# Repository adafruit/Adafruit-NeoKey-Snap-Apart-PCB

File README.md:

## Adafruit NeoKey Snap-Apart 5x6 Ortho Mechanical Key Switches with NeoPixel PCB

<a href="http://www.adafruit.com/products/5157"><br/>
Click here to purchase one from the Adafruit shop</a>

PCB files for the Adafruit NeoKey Snap-Apart 5x6 Ortho Mechanical Key Switches with NeoPixel. 

Format is EagleCAD schematic and board layout
* https://www.adafruit.com/product/5157

### Description

For folks who want ready-to-go keeb action, we've got the lovely Adafruit Macropad with a 3x4 grid of MX+NeoPixel key switches - but for those who like to forge their own path, we now present the easiest way of creating custom ortholinear (that's a fancy word for gridded) key matrices. Instead of hand soldering together a custom matrix of NeoKey socket breakouts, the Adafruit NeoKey 5x6 Ortho Snap-Apart Mechanical Key Switches with NeoPixel has 30 key switches that can be snapped apart to make any size grid.

That's right! Even though it comes as 5x6, you can turn it into 2x3, 1x6, 4x3...whatever you wish, and it will work just the way you expect. The little break-apart tabs have traces running through them that pass the power, NeoPixel, and keymatrix lines up and down.

Each 'sub-key' is the same - with a column and row line that is diode protected. For whatever grid size you eventually choose, connect a digital IO pin from your microcontroller to each of the outer rows and columns. With the diode, you don't have to worry about key ghosting.

If you want to add glowy goodness, that's even easier. Each key also has a single reverse-mount NeoPixel pointing up through the spot where many switches would have an LED to shine through. Connect 3 to 5V power to any of the + and - pins on the grid, and connect a single digital IO line to the beginning of the 'NeoPixel snake' that winds its way through the matrix. A weak 2.2K pass-through resistor will shunt data through at the end of each row, so you don't have to do any jumpering unless the matrix is not-rectangular.

Every breakout has a Kailh socket, which means you can plug in any MX-compatible switch instead of soldering it in. You may need a little glue to keep the switch in place: hot glue or a dot of epoxy worked fine for us. The sub-keys are spaced 0.75" apart for compact keebing. There's large 0.125" mounting holes at the corners of each key for easy mounting to a backplane.

Please note, each order comes with one sheet of assembled PCBs that can be broken apart - we include top and bottom railing bits to help keep it nice and flat during shipment. Once the grid is broken, you could jumper the breakout pads together to re-connect but it won't be very fun. Mechanical switches and keycaps are not included! Use any MX-compatible switch: Kailh, Gateron, etc all work!

### License

Adafruit invests time and resources providing this open source design, please support Adafruit and open-source hardware by purchasing products from [Adafruit](https://www.adafruit.com)!

Designed by Limor Fried/Ladyada for Adafruit Industries.

Creative Commons Attribution/Share-Alike, all text above must be included in any redistribution. 
See license.txt for additional details.

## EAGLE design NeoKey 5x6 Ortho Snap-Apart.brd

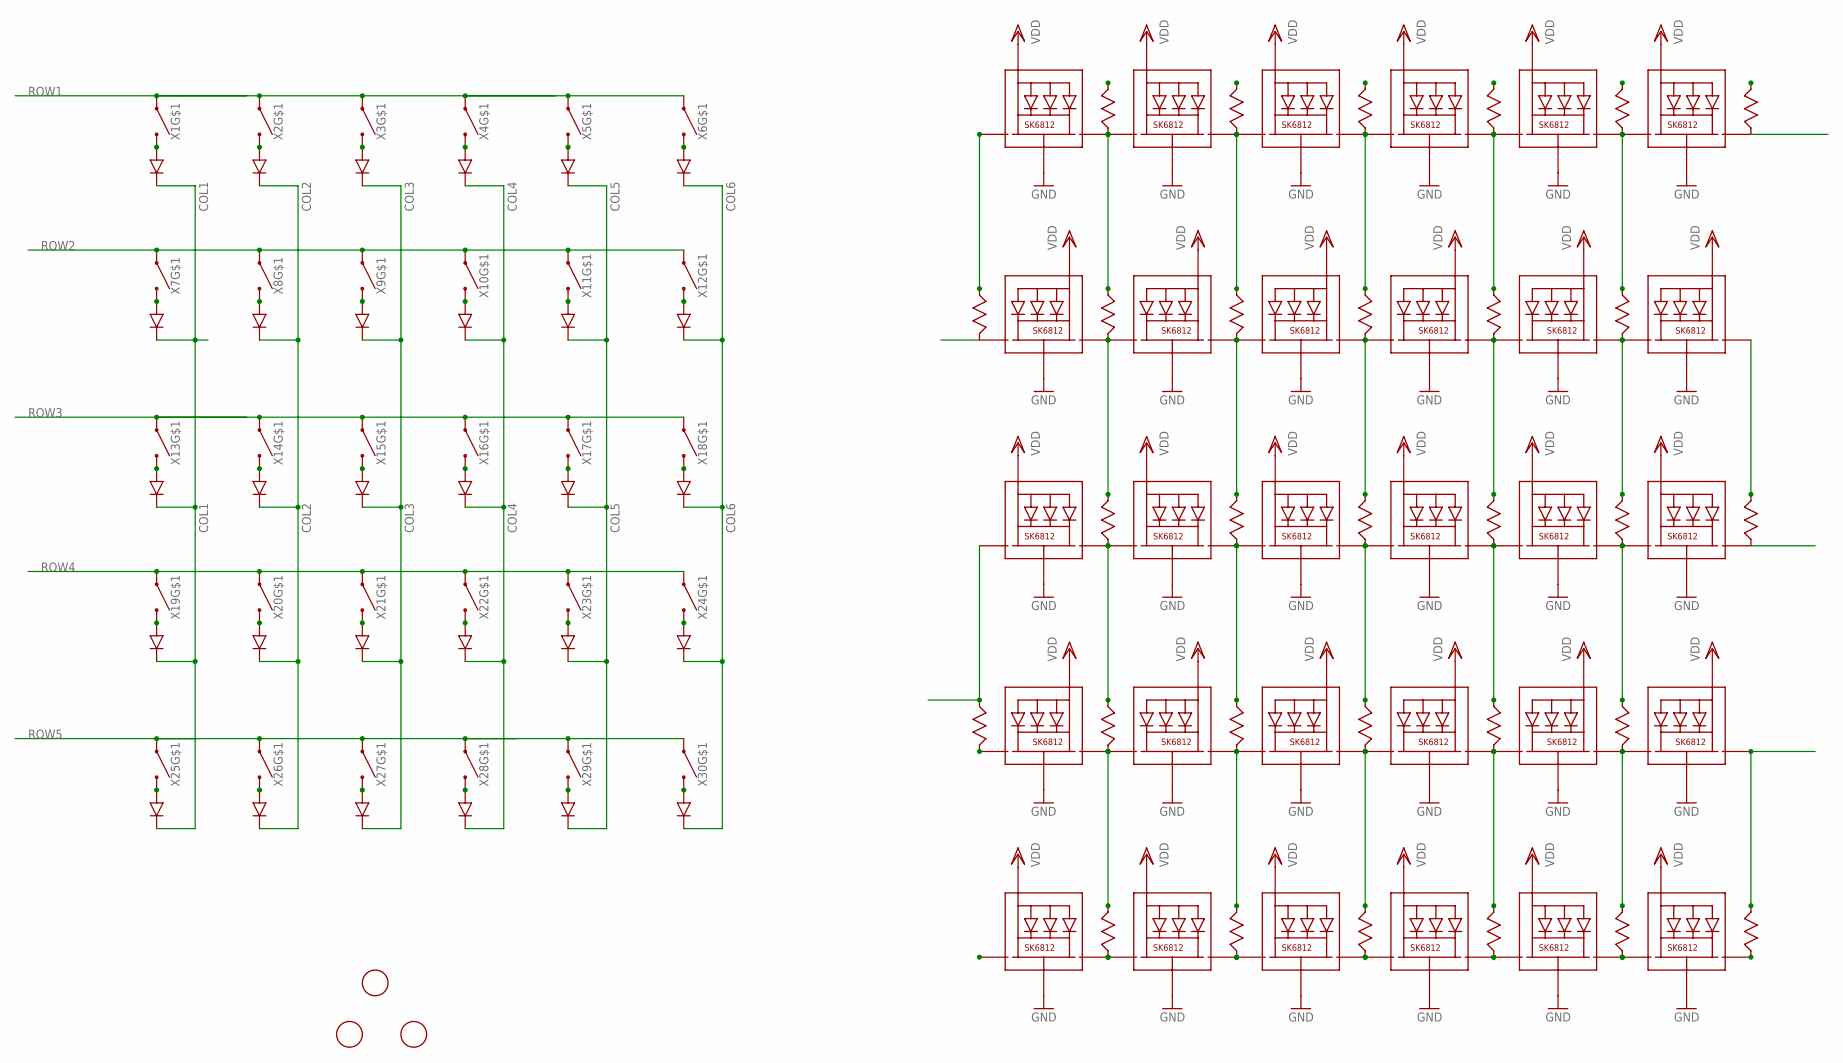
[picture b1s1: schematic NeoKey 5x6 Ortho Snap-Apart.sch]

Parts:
U$1, U$2, U$3: FIDUCIAL; FIDUCIAL_1MM
X1, X2, X3, X4, X5, X6, X13, X14, X15, X16, X17, X18, X25, X26, X27, X28, X29, X30: KAILH_SOCKET_TILE
X7, X8, X9, X10, X11, X12, X19, X20, X21, X22, X23, X24: KAILH_SOCKET_TILE_REVERSE; KAILH_SOCKET_TILE_REV

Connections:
COL1: X1.C (SW_C), X1.C1 (SW_C), X1.C2 (SW_C), X7.C (SW_C), X7.C1 (SW_C), X7.C2 (SW_C), X13.C (SW_C), X13.C1 (SW_C), X13.C2 (SW_C), X19.C (SW_C), X19.C1 (SW_C), X19.C2 (SW_C), X25.C (SW_C), X25.C1 (SW_C), X25.C2 (SW_C)
COL2: X2.C (SW_C), X2.C1 (SW_C), X2.C2 (SW_C), X8.C (SW_C), X8.C1 (SW_C), X8.C2 (SW_C), X14.C (SW_C), X14.C1 (SW_C), X14.C2 (SW_C), X20.C (SW_C), X20.C1 (SW_C), X20.C2 (SW_C), X26.C (SW_C), X26.C1 (SW_C), X26.C2 (SW_C)
COL3: X3.C (SW_C), X3.C1 (SW_C), X3.C2 (SW_C), X9.C (SW_C), X9.C1 (SW_C), X9.C2 (SW_C), X15.C (SW_C), X15.C1 (SW_C), X15.C2 (SW_C), X21.C (SW_C), X21.C1 (SW_C), X21.C2 (SW_C), X27.C (SW_C), X27.C1 (SW_C), X27.C2 (SW_C)
COL4: X4.C (SW_C), X4.C1 (SW_C), X4.C2 (SW_C), X10.C (SW_C), X10.C1 (SW_C), X10.C2 (SW_C), X16.C (SW_C), X16.C1 (SW_C), X16.C2 (SW_C), X22.C (SW_C), X22.C1 (SW_C), X22.C2 (SW_C), X28.C (SW_C), X28.C1 (SW_C), X28.C2 (SW_C)
COL5: X5.C (SW_C), X5.C1 (SW_C), X5.C2 (SW_C), X11.C (SW_C), X11.C1 (SW_C), X11.C2 (SW_C), X17.C (SW_C), X17.C1 (SW_C), X17.C2 (SW_C), X23.C (SW_C), X23.C1 (SW_C), X23.C2 (SW_C), X29.C (SW_C), X29.C1 (SW_C), X29.C2 (SW_C)
COL6: X6.C (SW_C), X6.C1 (SW_C), X6.C2 (SW_C), X12.C (SW_C), X12.C1 (SW_C), X12.C2 (SW_C), X18.C (SW_C), X18.C1 (SW_C), X18.C2 (SW_C), X24.C (SW_C), X24.C1 (SW_C), X24.C2 (SW_C), X30.C (SW_C), X30.C1 (SW_C), X30.C2 (SW_C)
GND: X1.3-GND (GND), X1.C- (GND), X1.GND1 (GND), X1.GND2 (GND), X2.3-GND (GND), X2.C- (GND), X2.GND1 (GND), X2.GND2 (GND), X3.3-GND (GND), X3.C- (GND), X3.GND1 (GND), X3.GND2 (GND), X4.3-GND (GND), X4.C- (GND), X4.GND1 (GND), X4.GND2 (GND), X5.3-GND (GND), X5.C- (GND), X5.GND1 (GND), X5.GND2 (GND), X6.3-GND (GND), X6.C- (GND), X6.GND1 (GND), X6.GND2 (GND), X7.3-GND (GND), X7.C- (GND), X7.GND1 (GND), X7.GND2 (GND), X8.3-GND (GND), X8.C- (GND), X8.GND1 (GND), X8.GND2 (GND), X9.3-GND (GND), X9.C- (GND), X9.GND1 (GND), X9.GND2 (GND), X10.3-GND (GND), X10.C- (GND), X10.GND1 (GND), X10.GND2 (GND), X11.3-GND (GND), X11.C- (GND), X11.GND1 (GND), X11.GND2 (GND), X12.3-GND (GND), X12.C- (GND), X12.GND1 (GND), X12.GND2 (GND), X13.3-GND (GND), X13.C- (GND), X13.GND1 (GND), X13.GND2 (GND), X14.3-GND (GND), X14.C- (GND), X14.GND1 (GND), X14.GND2 (GND), X15.3-GND (GND), X15.C- (GND), X15.GND1 (GND), X15.GND2 (GND), X16.3-GND (GND), X16.C- (GND), X16.GND1 (GND), X16.GND2 (GND), X17.3-GND (GND), X17.C- (GND), X17.GND1 (GND), X17.GND2 (GND), X18.3-GND (GND), X18.C- (GND), X18.GND1 (GND), X18.GND2 (GND), X19.3-GND (GND), X19.C- (GND), X19.GND1 (GND), X19.GND2 (GND), X20.3-GND (GND), X20.C- (GND), X20.GND1 (GND), X20.GND2 (GND), X21.3-GND (GND), X21.C- (GND), X21.GND1 (GND), X21.GND2 (GND), X22.3-GND (GND), X22.C- (GND), X22.GND1 (GND), X22.GND2 (GND), X23.3-GND (GND), X23.C- (GND), X23.GND1 (GND), X23.GND2 (GND), X24.3-GND (GND), X24.C- (GND), X24.GND1 (GND), X24.GND2 (GND), X25.3-GND (GND), X25.C- (GND), X25.GND1 (GND), X25.GND2 (GND), X26.3-GND (GND), X26.C- (GND), X26.GND1 (GND), X26.GND2 (GND), X27.3-GND (GND), X27.C- (GND), X27.GND1 (GND), X27.GND2 (GND), X28.3-GND (GND), X28.C- (GND), X28.GND1 (GND), X28.GND2 (GND), X29.3-GND (GND), X29.C- (GND), X29.GND1 (GND), X29.GND2 (GND), X30.3-GND (GND), X30.C- (GND), X30.GND1 (GND), X30.GND2 (GND)
unnamed: X1.4-DIN (DI), X1.DIN (DI), X1.DIN1 (DI), X2.2-DOUT (DO), X2.DOUT (DO), X2.DOUT1 (DO), X8.DIN_C (DI1), X8.DIN_C1 (DI1)
unnamed: X1.D+ (DA), X1.DA
unnamed: X1.DIN_C (DI1), X1.DIN_C1 (DI1)
unnamed: X2.D+ (DA), X2.DA
unnamed: X4.D+ (DA), X4.DA
unnamed: X1.2-DOUT (DO), X1.DOUT (DO), X1.DOUT1 (DO), X7.DIN_C (DI1), X7.DIN_C1 (DI1)
unnamed: X7.D+ (DA), X7.DA
unnamed: X2.DIN_C (DI1), X2.DIN_C1 (DI1)
unnamed: X3.D+ (DA), X3.DA
unnamed: X2.4-DIN (DI), X2.DIN (DI), X2.DIN1 (DI), X3.2-DOUT (DO), X3.DOUT (DO), X3.DOUT1 (DO), X9.DIN_C (DI1), X9.DIN_C1 (DI1)
unnamed: X3.4-DIN (DI), X3.DIN (DI), X3.DIN1 (DI), X4.2-DOUT (DO), X4.DOUT (DO), X4.DOUT1 (DO), X10.DIN_C (DI1), X10.DIN_C1 (DI1)
unnamed: X3.DIN_C (DI1), X3.DIN_C1 (DI1)
unnamed: X4.4-DIN (DI), X4.DIN (DI), X4.DIN1 (DI), X5.2-DOUT (DO), X5.DOUT (DO), X5.DOUT1 (DO), X11.DIN_C (DI1), X11.DIN_C1 (DI1)
unnamed: X4.DIN_C (DI1), X4.DIN_C1 (DI1)
unnamed: X6.D+ (DA), X6.DA
unnamed: X5.4-DIN (DI), X5.DIN (DI), X5.DIN1 (DI), X6.2-DOUT (DO), X6.DOUT (DO), X6.DOUT1 (DO), X12.DIN_C (DI1), X12.DIN_C1 (DI1)
unnamed: X12.2-DOUT (DO), X12.DOUT (DO), X12.DOUT1 (DO), X18.DIN_C (DI1), X18.DIN_C1 (DI1)
unnamed: X6.DIN_C (DI1), X6.DIN_C1 (DI1)
unnamed: X5.D+ (DA), X5.DA
unnamed: X5.DIN_C (DI1), X5.DIN_C1 (DI1)
unnamed: X6.4-DIN (DI), X6.DIN (DI), X6.DIN1 (DI)
unnamed: X13.D+ (DA), X13.DA
unnamed: X8.D+ (DA), X8.DA
unnamed: X8.2-DOUT (DO), X8.DOUT (DO), X8.DOUT1 (DO), X9.4-DIN (DI), X9.DIN (DI), X9.DIN1 (DI), X14.DIN_C (DI1), X14.DIN_C1 (DI1)
unnamed: X13.2-DOUT (DO), X13.DOUT (DO), X13.DOUT1 (DO), X19.DIN_C (DI1), X19.DIN_C1 (DI1)
unnamed: X9.D+ (DA), X9.DA
unnamed: X9.2-DOUT (DO), X9.DOUT (DO), X9.DOUT1 (DO), X10.4-DIN (DI), X10.DIN (DI), X10.DIN1 (DI), X15.DIN_C (DI1), X15.DIN_C1 (DI1)
unnamed: X13.4-DIN (DI), X13.DIN (DI), X13.DIN1 (DI), X14.2-DOUT (DO), X14.DOUT (DO), X14.DOUT1 (DO), X20.DIN_C (DI1), X20.DIN_C1 (DI1)
unnamed: X10.D+ (DA), X10.DA
unnamed: X10.2-DOUT (DO), X10.DOUT (DO), X10.DOUT1 (DO), X11.4-DIN (DI), X11.DIN (DI), X11.DIN1 (DI), X16.DIN_C (DI1), X16.DIN_C1 (DI1)
unnamed: X7.2-DOUT (DO), X7.DOUT (DO), X7.DOUT1 (DO), X8.4-DIN (DI), X8.DIN (DI), X8.DIN1 (DI), X13.DIN_C (DI1), X13.DIN_C1 (DI1)
unnamed: X11.D+ (DA), X11.DA
unnamed: X11.2-DOUT (DO), X11.DOUT (DO), X11.DOUT1 (DO), X12.4-DIN (DI), X12.DIN (DI), X12.DIN1 (DI), X17.DIN_C (DI1), X17.DIN_C1 (DI1)
unnamed: X15.D+ (DA), X15.DA
unnamed: X12.D+ (DA), X12.DA
unnamed: X14.4-DIN (DI), X14.DIN (DI), X14.DIN1 (DI), X15.2-DOUT (DO), X15.DOUT (DO), X15.DOUT1 (DO), X21.DIN_C (DI1), X21.DIN_C1 (DI1)
unnamed: X7.4-DIN (DI), X7.DIN (DI), X7.DIN1 (DI)
unnamed: X14.D+ (DA), X14.DA
unnamed: X25.D+ (DA), X25.DA
unnamed: X16.D+ (DA), X16.DA
unnamed: X16.4-DIN (DI), X16.DIN (DI), X16.DIN1 (DI), X17.2-DOUT (DO), X17.DOUT (DO), X17.DOUT1 (DO), X23.DIN_C (DI1), X23.DIN_C1 (DI1)
unnamed: X25.2-DOUT (DO), X25.DOUT (DO), X25.DOUT1 (DO)
unnamed: X18.D+ (DA), X18.DA
unnamed: X17.4-DIN (DI), X17.DIN (DI), X17.DIN1 (DI), X18.2-DOUT (DO), X18.DOUT (DO), X18.DOUT1 (DO), X24.DIN_C (DI1), X24.DIN_C1 (DI1)
unnamed: X18.4-DIN (DI), X18.DIN (DI), X18.DIN1 (DI)
unnamed: X25.4-DIN (DI), X25.DIN (DI), X25.DIN1 (DI), X26.2-DOUT (DO), X26.DOUT (DO), X26.DOUT1 (DO)
unnamed: X17.D+ (DA), X17.DA
unnamed: X15.4-DIN (DI), X15.DIN (DI), X15.DIN1 (DI), X16.2-DOUT (DO), X16.DOUT (DO), X16.DOUT1 (DO), X22.DIN_C (DI1), X22.DIN_C1 (DI1)
unnamed: X19.D+ (DA), X19.DA
unnamed: X19.2-DOUT (DO), X19.DOUT (DO), X19.DOUT1 (DO), X20.4-DIN (DI), X20.DIN (DI), X20.DIN1 (DI), X25.DIN_C (DI1), X25.DIN_C1 (DI1)
unnamed: X19.4-DIN (DI), X19.DIN (DI), X19.DIN1 (DI)
unnamed: X20.D+ (DA), X20.DA
unnamed: X20.2-DOUT (DO), X20.DOUT (DO), X20.DOUT1 (DO), X21.4-DIN (DI), X21.DIN (DI), X21.DIN1 (DI), X26.DIN_C (DI1), X26.DIN_C1 (DI1)
unnamed: X21.D+ (DA), X21.DA
unnamed: X22.D+ (DA), X22.DA
unnamed: X22.2-DOUT (DO), X22.DOUT (DO), X22.DOUT1 (DO), X23.4-DIN (DI), X23.DIN (DI), X23.DIN1 (DI), X28.DIN_C (DI1), X28.DIN_C1 (DI1)
unnamed: X23.D+ (DA), X23.DA
unnamed: X23.2-DOUT (DO), X23.DOUT (DO), X23.DOUT1 (DO), X24.4-DIN (DI), X24.DIN (DI), X24.DIN1 (DI), X29.DIN_C (DI1), X29.DIN_C1 (DI1)
unnamed: X24.D+ (DA), X24.DA
unnamed: X27.D+ (DA), X27.DA
unnamed: X26.4-DIN (DI), X26.DIN (DI), X26.DIN1 (DI), X27.2-DOUT (DO), X27.DOUT (DO), X27.DOUT1 (DO)
unnamed: X21.2-DOUT (DO), X21.DOUT (DO), X21.DOUT1 (DO), X22.4-DIN (DI), X22.DIN (DI), X22.DIN1 (DI), X27.DIN_C (DI1), X27.DIN_C1 (DI1)
unnamed: X26.D+ (DA), X26.DA
unnamed: X28.D+ (DA), X28.DA
unnamed: X28.4-DIN (DI), X28.DIN (DI), X28.DIN1 (DI), X29.2-DOUT (DO), X29.DOUT (DO), X29.DOUT1 (DO)
unnamed: X30.D+ (DA), X30.DA
unnamed: X29.4-DIN (DI), X29.DIN (DI), X29.DIN1 (DI), X30.2-DOUT (DO), X30.DOUT (DO), X30.DOUT1 (DO)
unnamed: X30.4-DIN (DI), X30.DIN (DI), X30.DIN1 (DI)
unnamed: X24.2-DOUT (DO), X24.DOUT (DO), X24.DOUT1 (DO), X30.DIN_C (DI1), X30.DIN_C1 (DI1)
unnamed: X29.D+ (DA), X29.DA
unnamed: X27.4-DIN (DI), X27.DIN (DI), X27.DIN1 (DI), X28.2-DOUT (DO), X28.DOUT (DO), X28.DOUT1 (DO)
ROW1: X1.A (SW_A), X1.A1 (SW_A), X1.A2 (SW_A), X2.A (SW_A), X2.A1 (SW_A), X2.A2 (SW_A), X3.A (SW_A), X3.A1 (SW_A), X3.A2 (SW_A), X4.A (SW_A), X4.A1 (SW_A), X4.A2 (SW_A), X5.A (SW_A), X5.A1 (SW_A), X5.A2 (SW_A), X6.A (SW_A), X6.A1 (SW_A), X6.A2 (SW_A)
ROW2: X7.A (SW_A), X7.A1 (SW_A), X7.A2 (SW_A), X8.A (SW_A), X8.A1 (SW_A), X8.A2 (SW_A), X9.A (SW_A), X9.A1 (SW_A), X9.A2 (SW_A), X10.A (SW_A), X10.A1 (SW_A), X10.A2 (SW_A), X11.A (SW_A), X11.A1 (SW_A), X11.A2 (SW_A), X12.A (SW_A), X12.A1 (SW_A), X12.A2 (SW_A)
ROW3: X13.A (SW_A), X13.A1 (SW_A), X13.A2 (SW_A), X14.A (SW_A), X14.A1 (SW_A), X14.A2 (SW_A), X15.A (SW_A), X15.A1 (SW_A), X15.A2 (SW_A), X16.A (SW_A), X16.A1 (SW_A), X16.A2 (SW_A), X17.A (SW_A), X17.A1 (SW_A), X17.A2 (SW_A), X18.A (SW_A), X18.A1 (SW_A), X18.A2 (SW_A)
ROW4: X19.A (SW_A), X19.A1 (SW_A), X19.A2 (SW_A), X20.A (SW_A), X20.A1 (SW_A), X20.A2 (SW_A), X21.A (SW_A), X21.A1 (SW_A), X21.A2 (SW_A), X22.A (SW_A), X22.A1 (SW_A), X22.A2 (SW_A), X23.A (SW_A), X23.A1 (SW_A), X23.A2 (SW_A), X24.A (SW_A), X24.A1 (SW_A), X24.A2 (SW_A)
ROW5: X25.A (SW_A), X25.A1 (SW_A), X25.A2 (SW_A), X26.A (SW_A), X26.A1 (SW_A), X26.A2 (SW_A), X27.A (SW_A), X27.A1 (SW_A), X27.A2 (SW_A), X28.A (SW_A), X28.A1 (SW_A), X28.A2 (SW_A), X29.A (SW_A), X29.A1 (SW_A), X29.A2 (SW_A), X30.A (SW_A), X30.A1 (SW_A), X30.A2 (SW_A)
VDD: X1.1-VDD (VDD), X1.C+ (VDD), X1.VDD1 (VDD), X1.VDD2 (VDD), X2.1-VDD (VDD), X2.C+ (VDD), X2.VDD1 (VDD), X2.VDD2 (VDD), X3.1-VDD (VDD), X3.C+ (VDD), X3.VDD1 (VDD), X3.VDD2 (VDD), X4.1-VDD (VDD), X4.C+ (VDD), X4.VDD1 (VDD), X4.VDD2 (VDD), X5.1-VDD (VDD), X5.C+ (VDD), X5.VDD1 (VDD), X5.VDD2 (VDD), X6.1-VDD (VDD), X6.C+ (VDD), X6.VDD1 (VDD), X6.VDD2 (VDD), X7.1-VDD (VDD), X7.C+ (VDD), X7.VDD1 (VDD), X7.VDD2 (VDD), X8.1-VDD (VDD), X8.C+ (VDD), X8.VDD1 (VDD), X8.VDD2 (VDD), X9.1-VDD (VDD), X9.C+ (VDD), X9.VDD1 (VDD), X9.VDD2 (VDD), X10.1-VDD (VDD), X10.C+ (VDD), X10.VDD1 (VDD), X10.VDD2 (VDD), X11.1-VDD (VDD), X11.C+ (VDD), X11.VDD1 (VDD), X11.VDD2 (VDD), X12.1-VDD (VDD), X12.C+ (VDD), X12.VDD1 (VDD), X12.VDD2 (VDD), X13.1-VDD (VDD), X13.C+ (VDD), X13.VDD1 (VDD), X13.VDD2 (VDD), X14.1-VDD (VDD), X14.C+ (VDD), X14.VDD1 (VDD), X14.VDD2 (VDD), X15.1-VDD (VDD), X15.C+ (VDD), X15.VDD1 (VDD), X15.VDD2 (VDD), X16.1-VDD (VDD), X16.C+ (VDD), X16.VDD1 (VDD), X16.VDD2 (VDD), X17.1-VDD (VDD), X17.C+ (VDD), X17.VDD1 (VDD), X17.VDD2 (VDD), X18.1-VDD (VDD), X18.C+ (VDD), X18.VDD1 (VDD), X18.VDD2 (VDD), X19.1-VDD (VDD), X19.C+ (VDD), X19.VDD1 (VDD), X19.VDD2 (VDD), X20.1-VDD (VDD), X20.C+ (VDD), X20.VDD1 (VDD), X20.VDD2 (VDD), X21.1-VDD (VDD), X21.C+ (VDD), X21.VDD1 (VDD), X21.VDD2 (VDD), X22.1-VDD (VDD), X22.C+ (VDD), X22.VDD1 (VDD), X22.VDD2 (VDD), X23.1-VDD (VDD), X23.C+ (VDD), X23.VDD1 (VDD), X23.VDD2 (VDD), X24.1-VDD (VDD), X24.C+ (VDD), X24.VDD1 (VDD), X24.VDD2 (VDD), X25.1-VDD (VDD), X25.C+ (VDD), X25.VDD1 (VDD), X25.VDD2 (VDD), X26.1-VDD (VDD), X26.C+ (VDD), X26.VDD1 (VDD), X26.VDD2 (VDD), X27.1-VDD (VDD), X27.C+ (VDD), X27.VDD1 (VDD), X27.VDD2 (VDD), X28.1-VDD (VDD), X28.C+ (VDD), X28.VDD1 (VDD), X28.VDD2 (VDD), X29.1-VDD (VDD), X29.C+ (VDD), X29.VDD1 (VDD), X29.VDD2 (VDD), X30.1-VDD (VDD), X30.C+ (VDD), X30.VDD1 (VDD), X30.VDD2 (VDD)

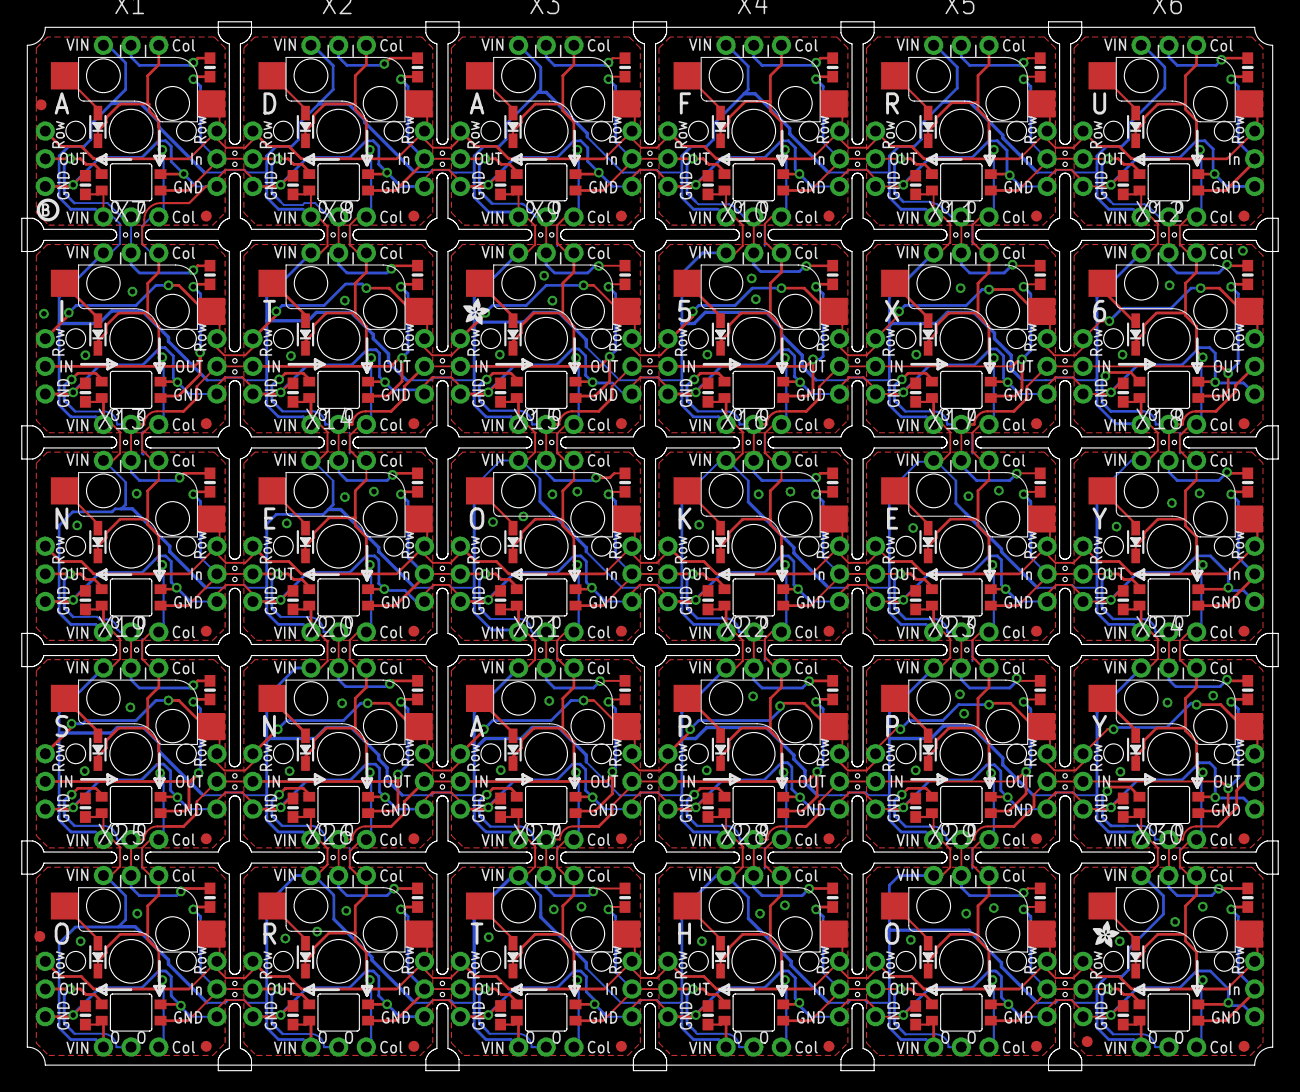
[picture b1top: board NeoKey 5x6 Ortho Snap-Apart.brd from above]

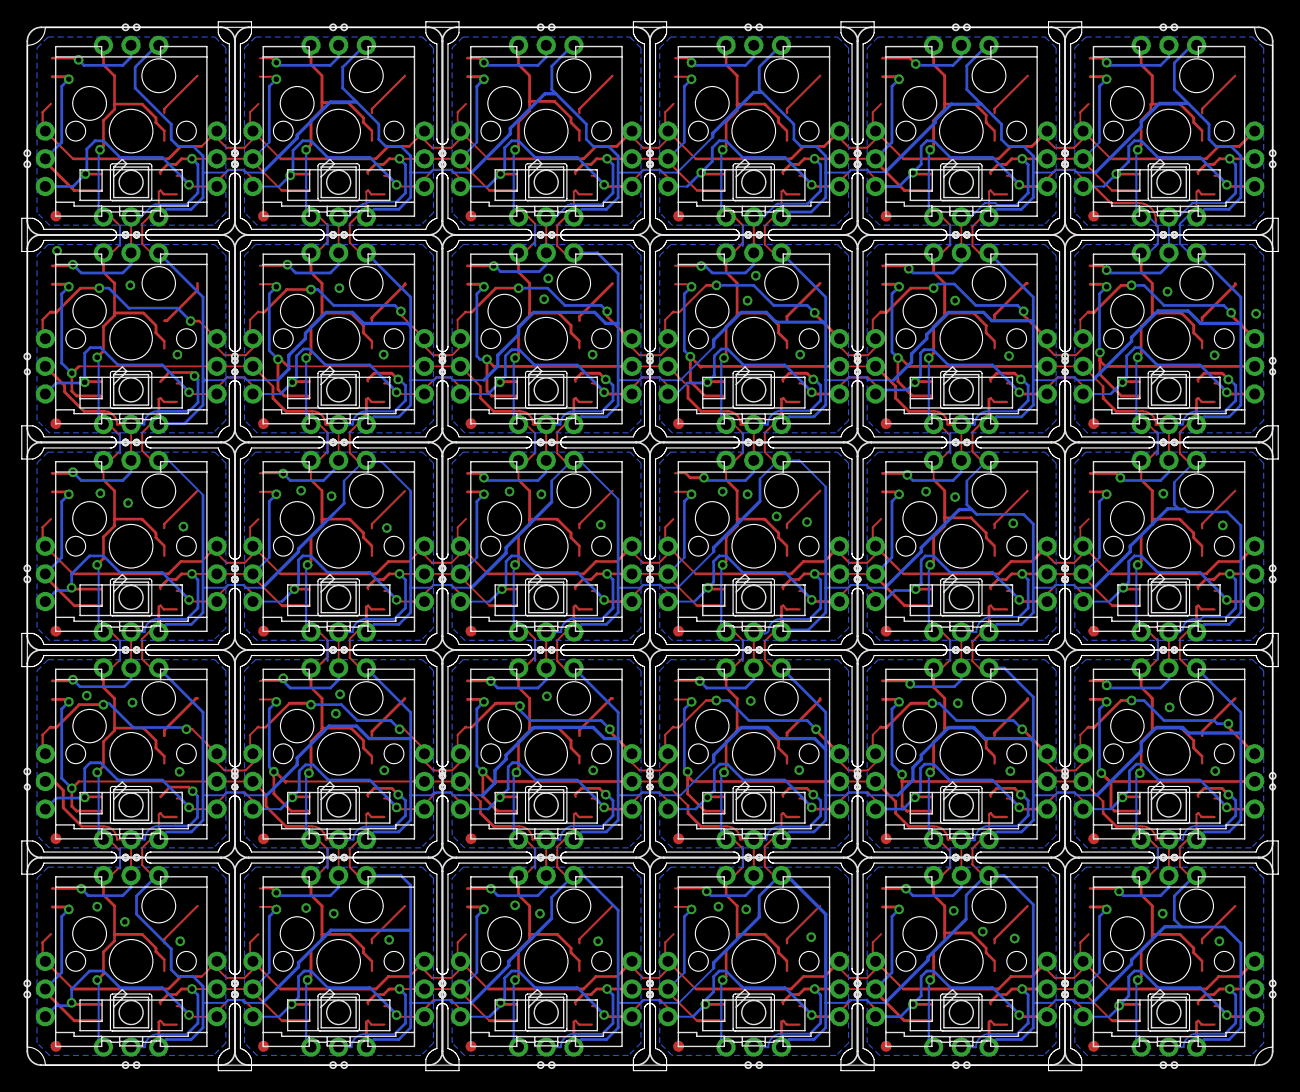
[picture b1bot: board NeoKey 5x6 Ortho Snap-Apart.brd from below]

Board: 2 copper layers, 115.3 x 96.3 mm, 36 parts (30 on the bottom side), 84 nets.

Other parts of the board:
U$4, U$5: ADAFRUIT_2.5MM
U$6: PCBFEAT-REV-040

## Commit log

2021-07-15 Adding board files.

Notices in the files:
parts and their libraries:
microbuilder: This work is placed in the public domain, and may be freely used for commercial and non-commercial work with the following conditions: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
